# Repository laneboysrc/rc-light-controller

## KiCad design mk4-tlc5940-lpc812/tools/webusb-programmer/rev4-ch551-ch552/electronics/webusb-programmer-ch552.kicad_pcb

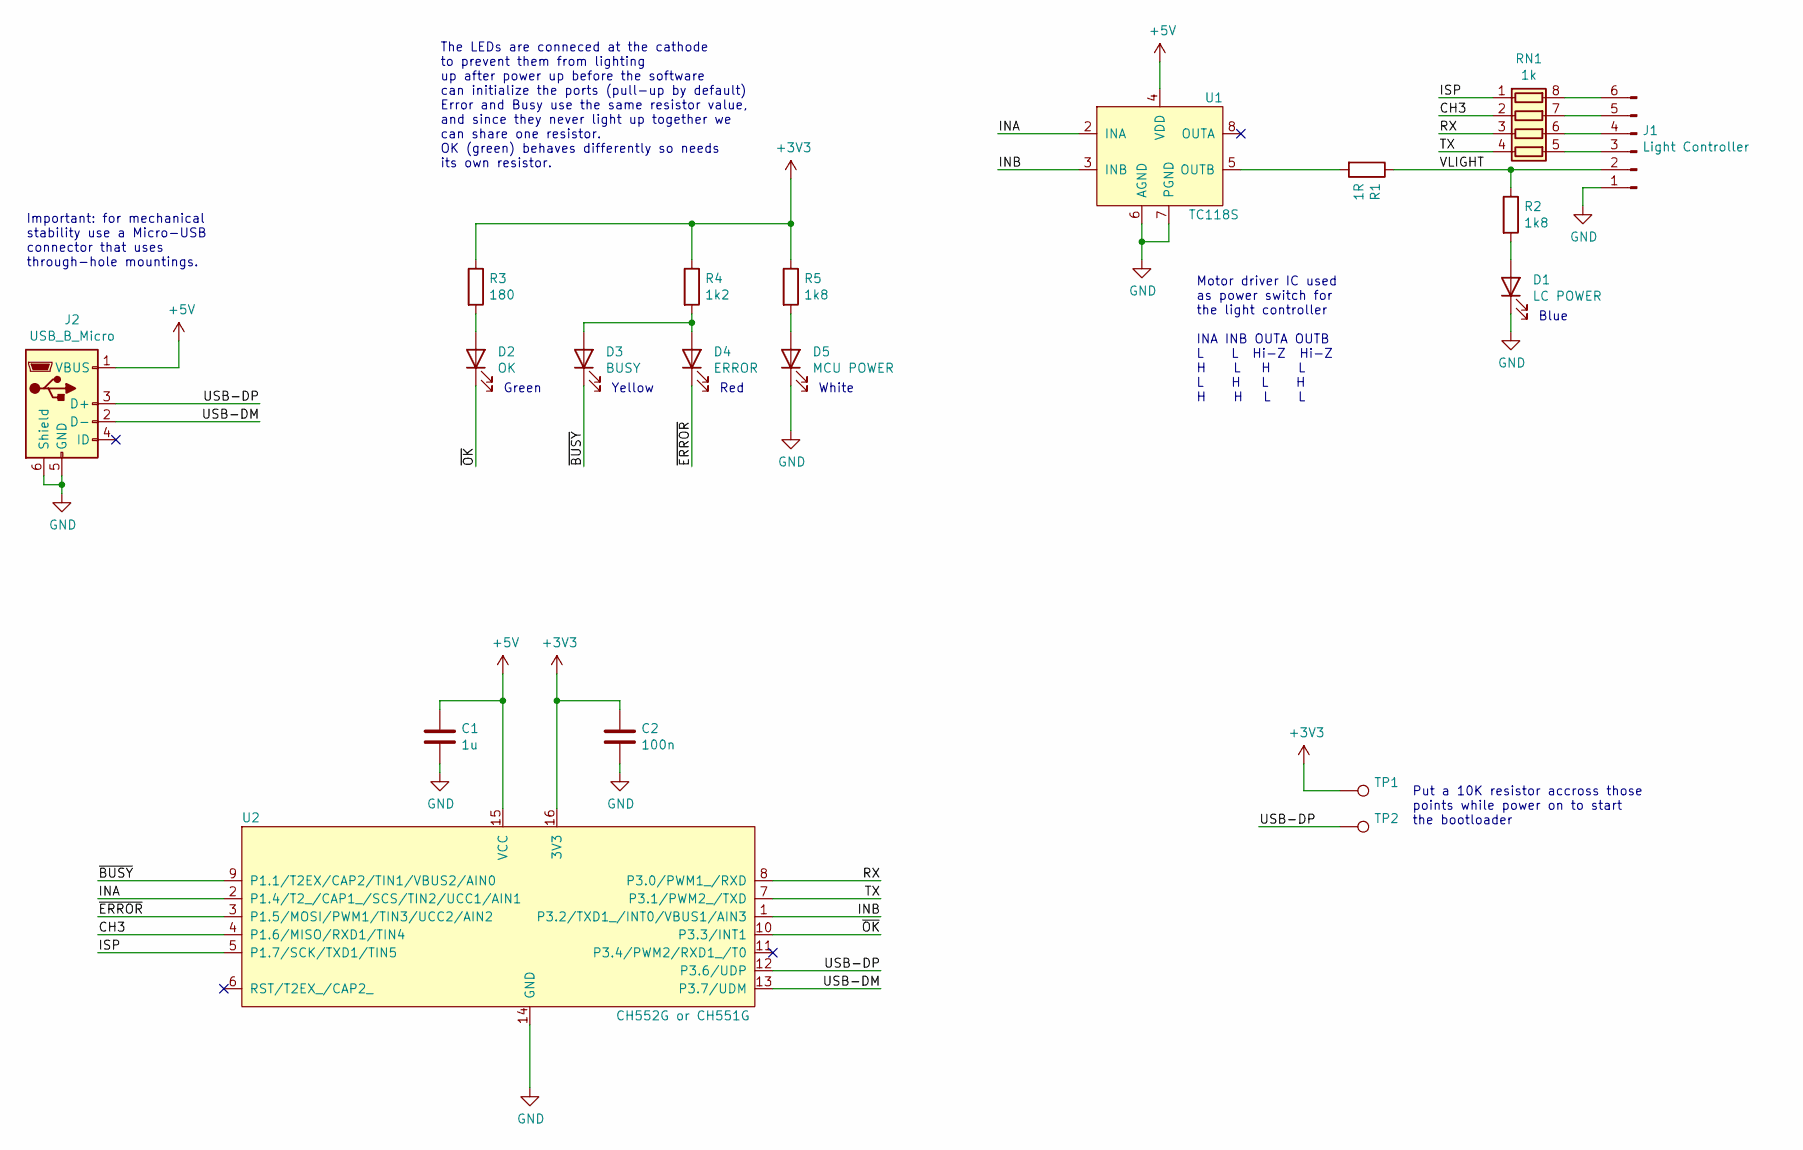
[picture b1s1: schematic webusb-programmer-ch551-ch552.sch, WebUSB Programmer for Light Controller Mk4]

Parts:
C1: 1u; C_0603_1608Metric
C2: 100n; C_0603_1608Metric
D1: LC POWER; LED_1204_side_mout; LCSC part number C779807
D2: OK; LED_1204_side_mout; LCSC part number C91608
D3: BUSY; LED_1204_side_mout; LCSC part number C779805
D4: ERROR; LED_1204_side_mout; LCSC part number C389527
D5: MCU POWER; LED_1204_side_mout; LCSC part number C779804
J1: Light Controller; PinHeader_1x06_P2.54mm_Flat
J2: USB_B_Micro; Mirco_USB_Type_B_LCSC_C40943; LCSC part number C40943
R1: 1R; R_0603_1608Metric_Pad0.98x0.95mm_HandSolder
R2, R5: 1k8; R_0603_1608Metric_Pad1.05x0.95mm_HandSolder
R3: 180; R_0603_1608Metric_Pad1.05x0.95mm_HandSolder
R4: 1k2; R_0603_1608Metric_Pad1.05x0.95mm_HandSolder
RN1: 1k; R_Array_Convex_4x0603
TP1, TP2: TestPoint_THTPad_1.0x1.0mm_Drill0.5mm_nosilk
U1: TC118S; SOP-8_3.9x4.9mm_P1.27mm
U2: CH552G or CH551G; SO-16_3.9x9.9mm_P1.27mm

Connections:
+3V3: C2.1, R3.1, R4.1, R5.1, TP1.1, U2.16 (3V3)
+5V: C1.1, J2.1 (VBUS), U1.4 (VDD), U2.15 (VCC)
/CH3: RN1.2 (R2.1), U2.4 (P1.6/MISO/RXD1/TIN4)
/INA: U1.2 (INA), U2.2 (P1.4/T2_/CAP1_/SCS/TIN2/UCC1/AIN1)
/INB: U1.3 (INB), U2.1 (P3.2/TXD1_/INT0/VBUS1/AIN3)
/ISP: RN1.1 (R1.1), U2.5 (P1.7/SCK/TXD1/TIN5)
/RX: RN1.3 (R3.1), U2.8 (P3.0/PWM1_/RXD)
/TX: RN1.4 (R4.1), U2.7 (P3.1/PWM2_/TXD)
/USB-DM: J2.2 (D-), U2.13 (P3.7/UDM)
/USB-DP: J2.3 (D+), TP2.1, U2.12 (P3.6/UDP)
/VLIGHT: J1.2, R1.1, R2.1
/~BUSY: D3.1 (K), U2.9 (P1.1/T2EX/CAP2/TIN1/VBUS2/AIN0)
/~ERROR: D4.1 (K), U2.3 (P1.5/MOSI/PWM1/TIN3/UCC2/AIN2)
/~OK: D2.1 (K), U2.10 (P3.3/INT1)
GND: C1.2, C2.2, D1.1 (K), D5.1 (K), J1.1, J2.5 (GND), J2.6 (Shield), U1.6 (AGND), U1.7 (PGND), U2.14 (GND)
unnamed: D1.2 (A), R2.2
unnamed: D2.2 (A), R3.2
unnamed: D3.2 (A), D4.2 (A), R4.2
unnamed: D5.2 (A), R5.2
unnamed: J1.3, RN1.5 (R4.2)
unnamed: J1.4, RN1.6 (R3.2)
unnamed: J1.5, RN1.7 (R2.2)
unnamed: J1.6, RN1.8 (R1.2)
unnamed: R1.2, U1.5 (OUTB)

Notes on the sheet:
Important: for mechanical stability use a Micro-USB connector that uses through-hole mountings.
White
Green
Yellow
Red
Blue
The LEDs are conneced at the cathode to prevent them from lighting up after power up before the software can initialize the ports (pull-up by default) Error and Busy use the same resistor value, and since they never light up together we can share one resistor. OK (green) behaves differently so need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
Put a 10K resistor accross those points while power on to start the bootloader
Motor driver IC used as power switch for the light controller INA INB OUTA OUTB L L Hi-Z Hi-Z H L H L L H L H H H L L

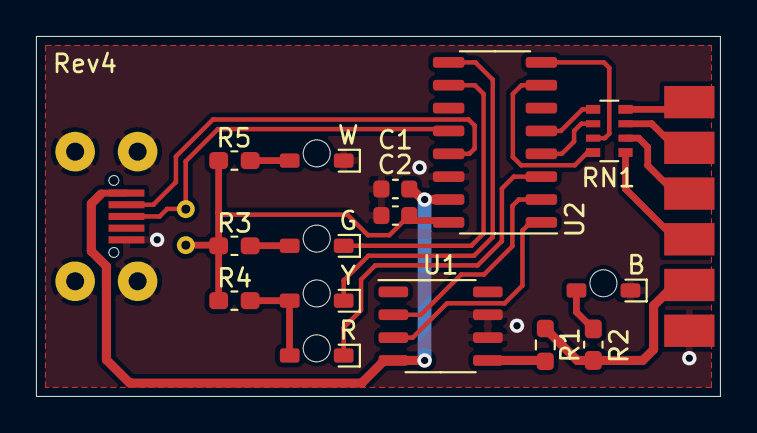
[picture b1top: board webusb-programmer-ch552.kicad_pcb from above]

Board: 2 copper layers, 38.0 x 20.0 mm, 19 parts (0 on the bottom side), 24 nets.

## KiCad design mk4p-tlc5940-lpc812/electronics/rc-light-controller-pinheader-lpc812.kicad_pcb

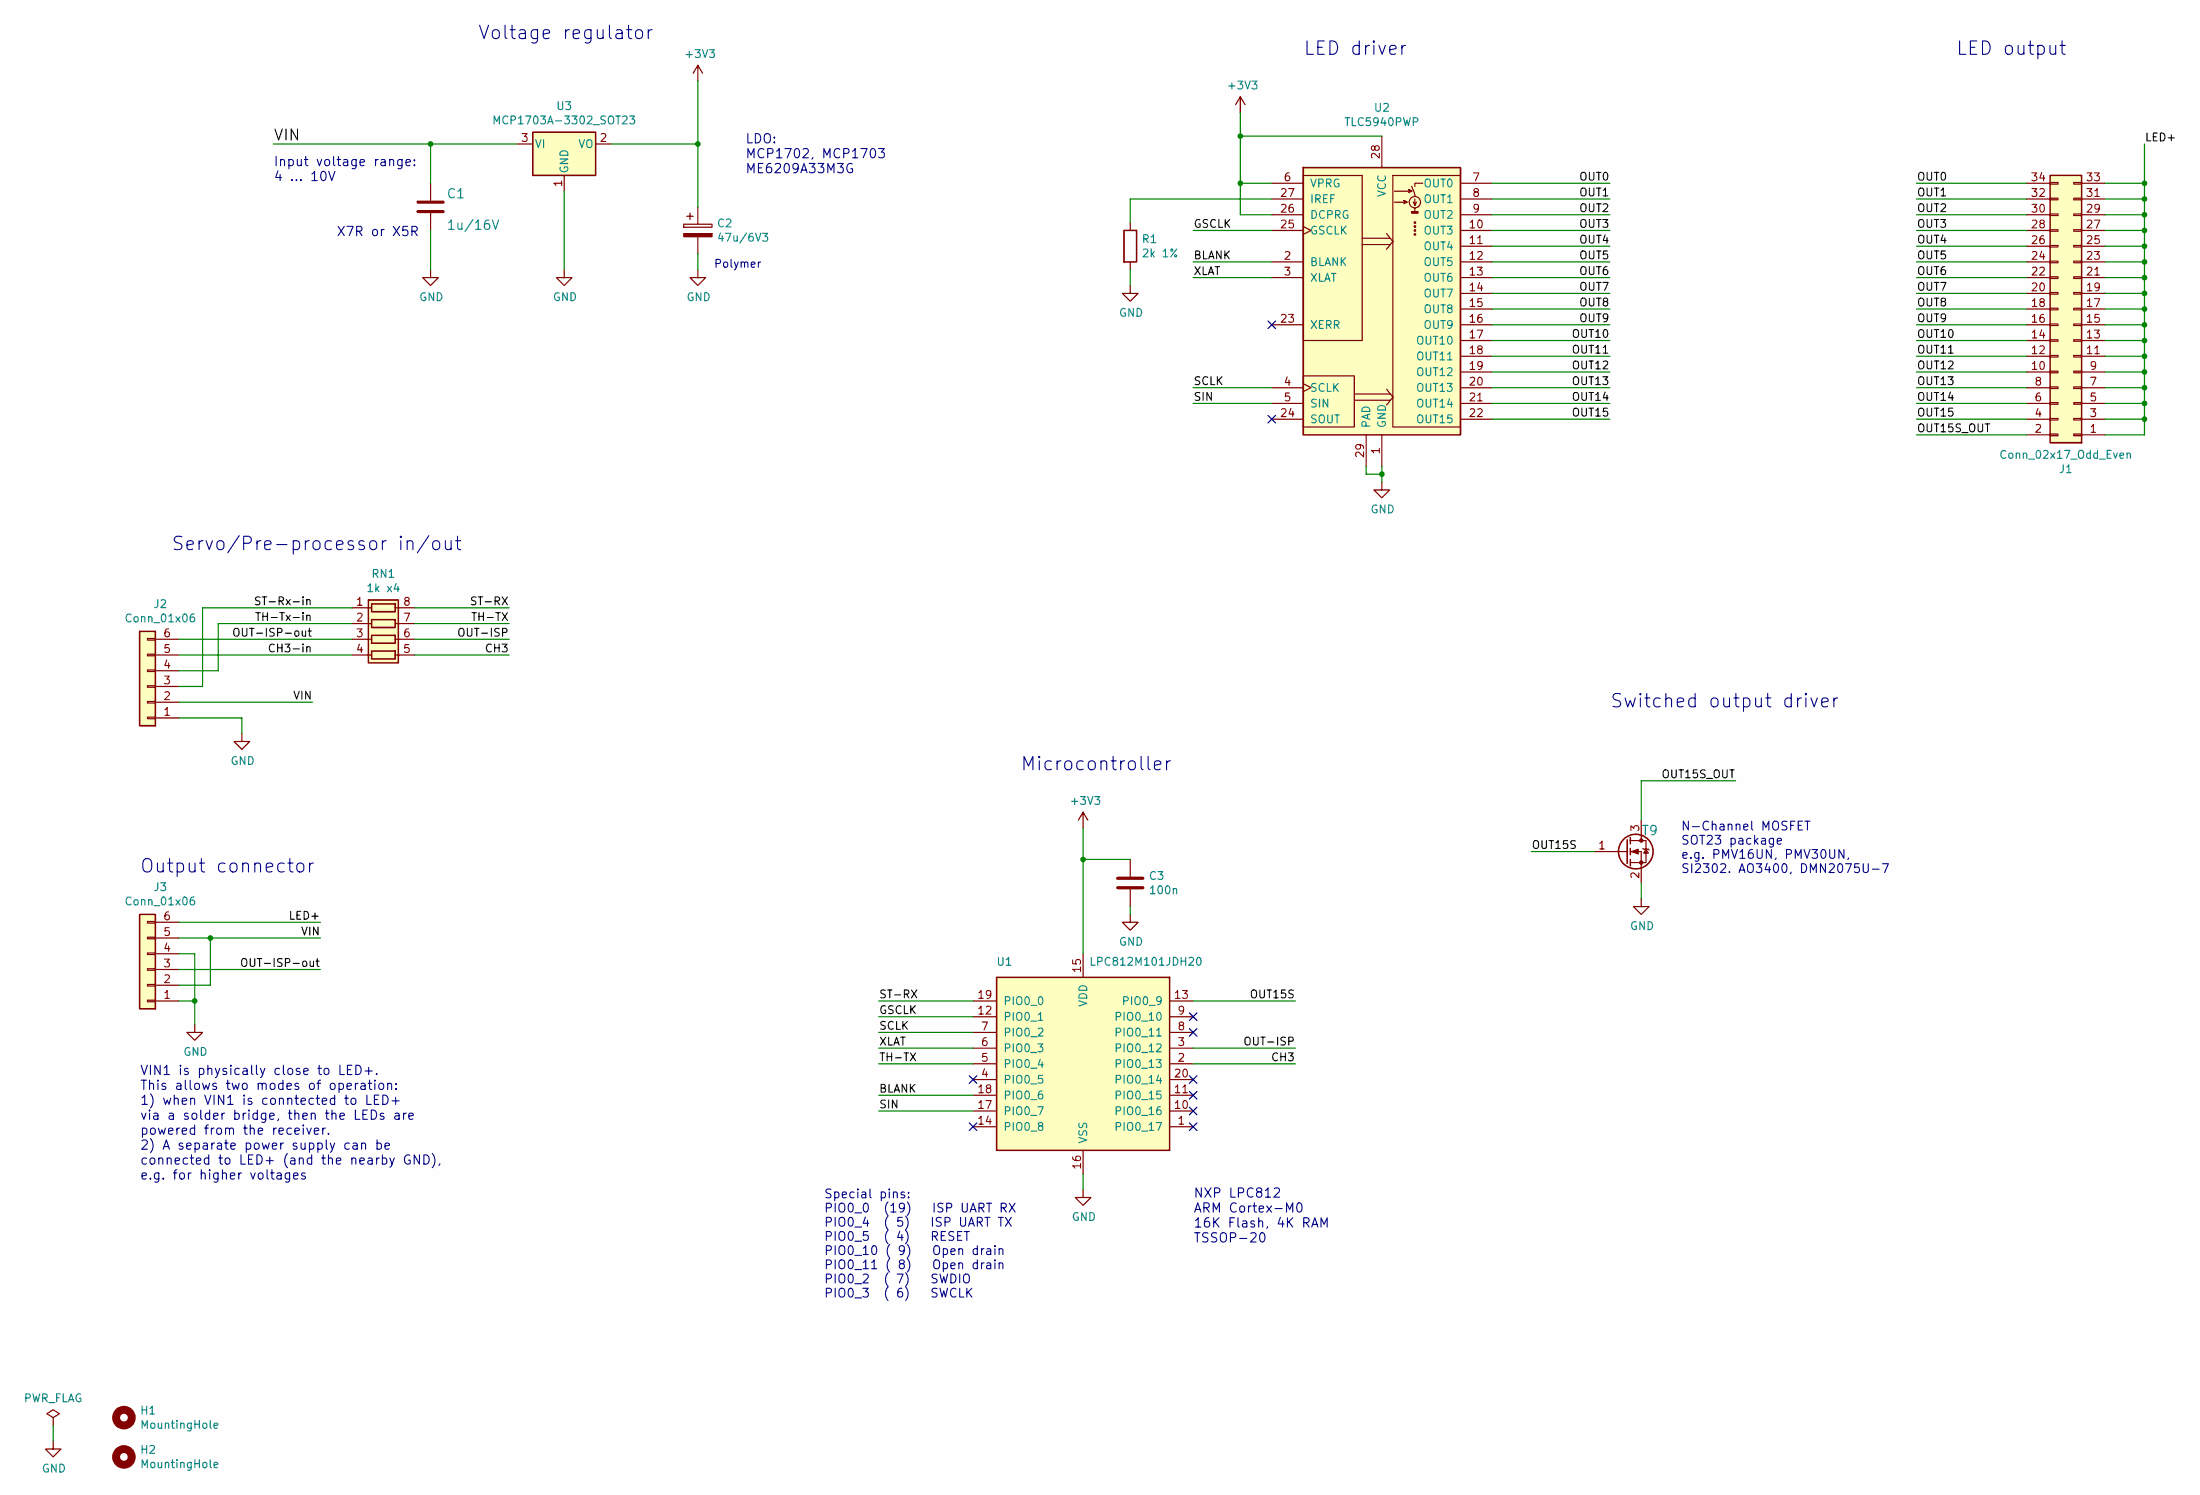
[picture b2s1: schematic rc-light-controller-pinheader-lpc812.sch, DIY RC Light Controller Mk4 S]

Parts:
C1: 1u/16V; C_0805_2012Metric
C2: 47u/6V3; C_0805_2012Metric
C3: 100n; C_0603_1608Metric
H1, H2: MountingHole; MountingHole_2.2mm_M2_ISO14580
J1: Conn_02x17_Odd_Even; PinHeader_2x17_P2.54mm_Horizontal
J2, J3: Conn_01x06; PinHeader_1x06_P2.54mm_Flat
R1: 2k 1%; R_0603_1608Metric
RN1: 1k x4; R_Array_Convex_4x0603
T9: NMOSSOT23; SOT-23
U1: LPC812M101JDH20; TSSOP-20_4.4x6.5mm_P0.65mm
U2: TLC5940PWP; SOP65P640X120-29N
U3: MCP1703A-3302_SOT23; SOT-23W

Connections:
+3V3: C2.1, C3.1, U1.15 (VDD), U2.6 (VPRG), U2.26 (DCPRG), U2.28 (VCC), U3.2 (VO)
/BLANK: U1.18 (PIO0_6), U2.2 (BLANK)
/CH3: RN1.5 (R4.2), U1.2 (PIO0_13)
/CH3-in: J2.5, RN1.4 (R4.1)
/GSCLK: U1.12 (PIO0_1), U2.25 (GSCLK)
/LED+: J1.1, J1.3, J1.5, J1.7, J1.9, J1.11, J1.13, J1.15, J1.17, J1.19, J1.21, J1.23, J1.25, J1.27, J1.29, J1.31, J1.33, J3.6
/OUT0: J1.34, U2.7 (OUT0)
/OUT1: J1.32, U2.8 (OUT1)
/OUT2: J1.30, U2.9 (OUT2)
/OUT3: J1.28, U2.10 (OUT3)
/OUT4: J1.26, U2.11 (OUT4)
/OUT5: J1.24, U2.12 (OUT5)
/OUT6: J1.22, U2.13 (OUT6)
/OUT7: J1.20, U2.14 (OUT7)
/OUT8: J1.18, U2.15 (OUT8)
/OUT9: J1.16, U2.16 (OUT9)
/OUT10: J1.14, U2.17 (OUT10)
/OUT11: J1.12, U2.18 (OUT11)
/OUT12: J1.10, U2.19 (OUT12)
/OUT13: J1.8, U2.20 (OUT13)
/OUT14: J1.6, U2.21 (OUT14)
/OUT15: J1.4, U2.22 (OUT15)
/OUT15S: T9.1 (G), U1.13 (PIO0_9)
/OUT15S_OUT: J1.2, T9.3 (D)
/OUT-ISP: RN1.6 (R3.2), U1.3 (PIO0_12)
/OUT-ISP-out: J2.6, J3.3, RN1.3 (R3.1)
/SCLK: U1.7 (PIO0_2), U2.4 (SCLK)
/SIN: U1.17 (PIO0_7), U2.5 (SIN)
/ST-RX: RN1.8 (R1.2), U1.19 (PIO0_0)
/ST-Rx-in: J2.3, RN1.1 (R1.1)
/TH-TX: RN1.7 (R2.2), U1.5 (PIO0_4)
/TH-Tx-in: J2.4, RN1.2 (R2.1)
/VIN: C1.1, J2.2, J3.2, J3.5, U3.3 (VI)
/XLAT: U1.6 (PIO0_3), U2.3 (XLAT)
GND: C1.2, C2.2, C3.2, J2.1, J3.1, J3.4, R1.2, T9.2 (S), U1.16 (VSS), U2.1 (GND), U2.29 (PAD), U3.1 (GND)
unnamed: R1.1, U2.27 (IREF)

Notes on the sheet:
Special pins: PIO0_0 (19) ISP UART RX PIO0_4 ( 5) ISP UART TX PIO0_5 ( 4) RESET PIO0_10 ( 9) Open drain PIO0_11 ( 8) Open drain PIO0_2 ( 7) SWDIO PIO0_3 ( 6) SWCLK
Servo/Pre-processor in/out
Voltage regulator
Microcontroller
X7R or X5R
Input voltage range: 4 ... 10V
LDO: MCP1702, MCP1703 ME6209A33M3G
NXP LPC812 ARM Cortex-M0 16K Flash, 4K RAM TSSOP-20
Polymer
LED output
VIN1 is physically close to LED+. This allows two modes of operation: 1) when VIN1 is conntected to LED+ via a solder bridge, then the LEDs are powered from the receiver. 2) A separate power supply can be connected to LED+ (and the nearby GND), e.g. for higher voltages
Output connector
N-Channel MOSFET SOT23 package e.g. PMV16UN, PMV30UN, SI2302. AO3400, DMN2075U-7
LED driver
Switched output driver

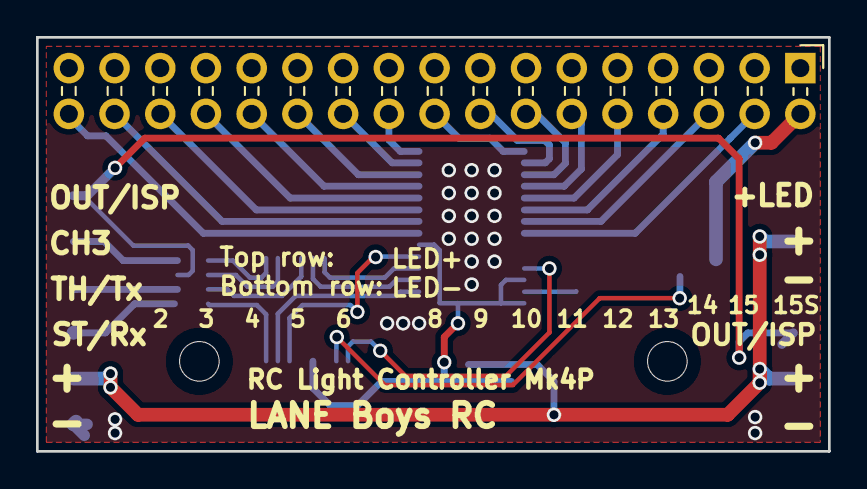
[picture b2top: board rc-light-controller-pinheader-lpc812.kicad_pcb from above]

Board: 2 copper layers, 44.0 x 23.0 mm, 14 parts (0 on the bottom side), 36 nets.

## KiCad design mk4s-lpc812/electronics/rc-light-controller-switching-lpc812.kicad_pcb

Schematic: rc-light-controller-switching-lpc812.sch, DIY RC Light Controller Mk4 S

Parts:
C1: 1u/16V; C_0805_2012Metric
C2: 47u/6V3; C_0805_2012Metric
C3: 100n; C_0603_1608Metric
H1, H2: MountingHole; MountingHole_2.2mm_M2_ISO14580
J1: Conn_02x17_Odd_Even; PinHeader_2x17_P2.54mm_Horizontal
J2, J3: Conn_01x06; PinHeader_1x06_P2.54mm_Flat
RN1: 1k x4; R_Array_Convex_4x0603
T1, T2, T3, T4, T5, T6, T7, T8, T9: NMOSSOT23; SOT-23
U1: LPC812M101JDH20; TSSOP-20_4.4x6.5mm_P0.65mm
U2: 3V3; SOT-23W

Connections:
/CH3: RN1.5 (R4.2), U1.2 (PIO0_13)
/CH3-in: J2.5, RN1.4 (R4.1)
/LED+: J1.1, J1.3, J1.5, J1.7, J1.9, J1.11, J1.13, J1.15, J1.17, J1.19, J1.21, J1.23, J1.25, J1.27, J1.29, J1.31, J1.33, J3.6
/OUT0: T1.1 (G), U1.1 (PIO0_17)
/OUT1: T2.1 (G), U1.6 (PIO0_3)
/OUT2: T3.1 (G), U1.7 (PIO0_2)
/OUT3: T4.1 (G), U1.10 (PIO0_16)
/OUT4: T5.1 (G), U1.17 (PIO0_7)
/OUT5: T6.1 (G), U1.14 (PIO0_8)
/OUT6: T7.1 (G), U1.13 (PIO0_9)
/OUT7: T8.1 (G), U1.12 (PIO0_1)
/OUT8: T9.1 (G), U1.11 (PIO0_15)
/OUT-ISP: RN1.6 (R3.2), U1.3 (PIO0_12)
/OUT-ISP-out: J2.6, J3.3, RN1.3 (R3.1)
/ST-RX: RN1.8 (R1.2), U1.19 (PIO0_0)
/ST-Rx-in: J2.3, RN1.1 (R1.1)
/TH-TX: RN1.7 (R2.2), U1.5 (PIO0_4)
/TH-Tx-in: J2.4, RN1.2 (R2.1)
/VIN: C1.1, J2.2, J3.2, J3.5, U2.3
GND: C1.2, C2.2, C3.2, J2.1, J3.1, J3.4, T1.2 (S), T2.2 (S), T3.2 (S), T4.2 (S), T5.2 (S), T6.2 (S), T7.2 (S), T8.2 (S), T9.2 (S), U1.16 (VSS), U2.1
unnamed: J1.2, T9.3 (D)
unnamed: J1.4, J1.6, T8.3 (D)
unnamed: J1.8, J1.10, T7.3 (D)
unnamed: J1.12, J1.14, T6.3 (D)
unnamed: J1.16, J1.18, T5.3 (D)
unnamed: J1.20, J1.22, T4.3 (D)
unnamed: J1.24, J1.26, T3.3 (D)
unnamed: J1.28, J1.30, T2.3 (D)
unnamed: J1.32, J1.34, T1.3 (D)

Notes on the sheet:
Special pins: PIO0_0 (19) ISP UART RX PIO0_4 ( 5) ISP UART TX PIO0_5 ( 4) RESET PIO0_10 ( 9) Open drain PIO0_11 ( 8) Open drain PIO0_2 ( 7) SWDIO PIO0_3 ( 6) SWCLK
Servo/Pre-processor in/out
Voltage regulator
Microcontroller
X7R or X5R
Input voltage range: 4 ... 10V
LDO: Microchip MCP1702 or MCP1703
NXP LPC812 ARM Cortex-M0 16K Flash, 4K RAM TSSOP-20
N-Channel MOSFET SOT23 package e.g. PMV16UN, PMV30UN, SI2302. AO3400, DMN2075U-7
Polymer
LED driver and outputs
VIN1 is physically close to LED+. This allows two modes of operation: 1) when VIN1 is conntected to LED+ via a solder bridge, then the LEDs are powered from the receiver. 2) A separate power supply can be connected to LED+ (and the nearby GND), e.g. for higher voltages
Output connector

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
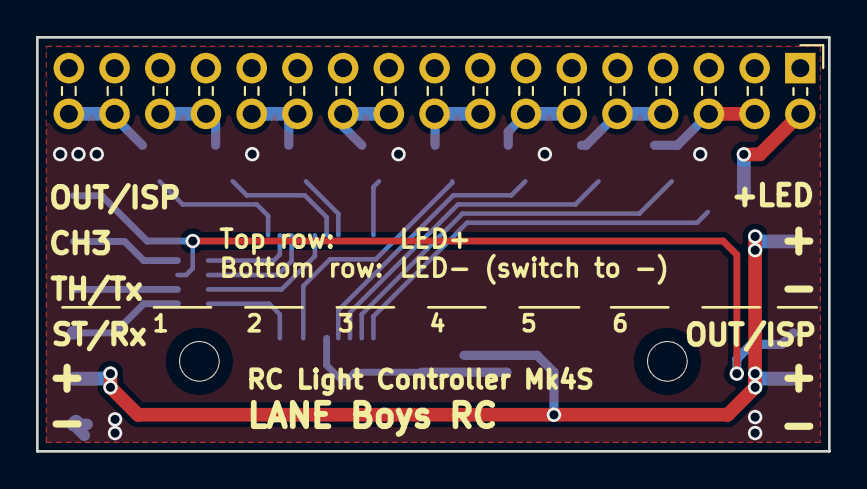
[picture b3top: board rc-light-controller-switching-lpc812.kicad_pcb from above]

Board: 2 copper layers, 44.0 x 23.0 mm, 20 parts (0 on the bottom side), 30 nets.

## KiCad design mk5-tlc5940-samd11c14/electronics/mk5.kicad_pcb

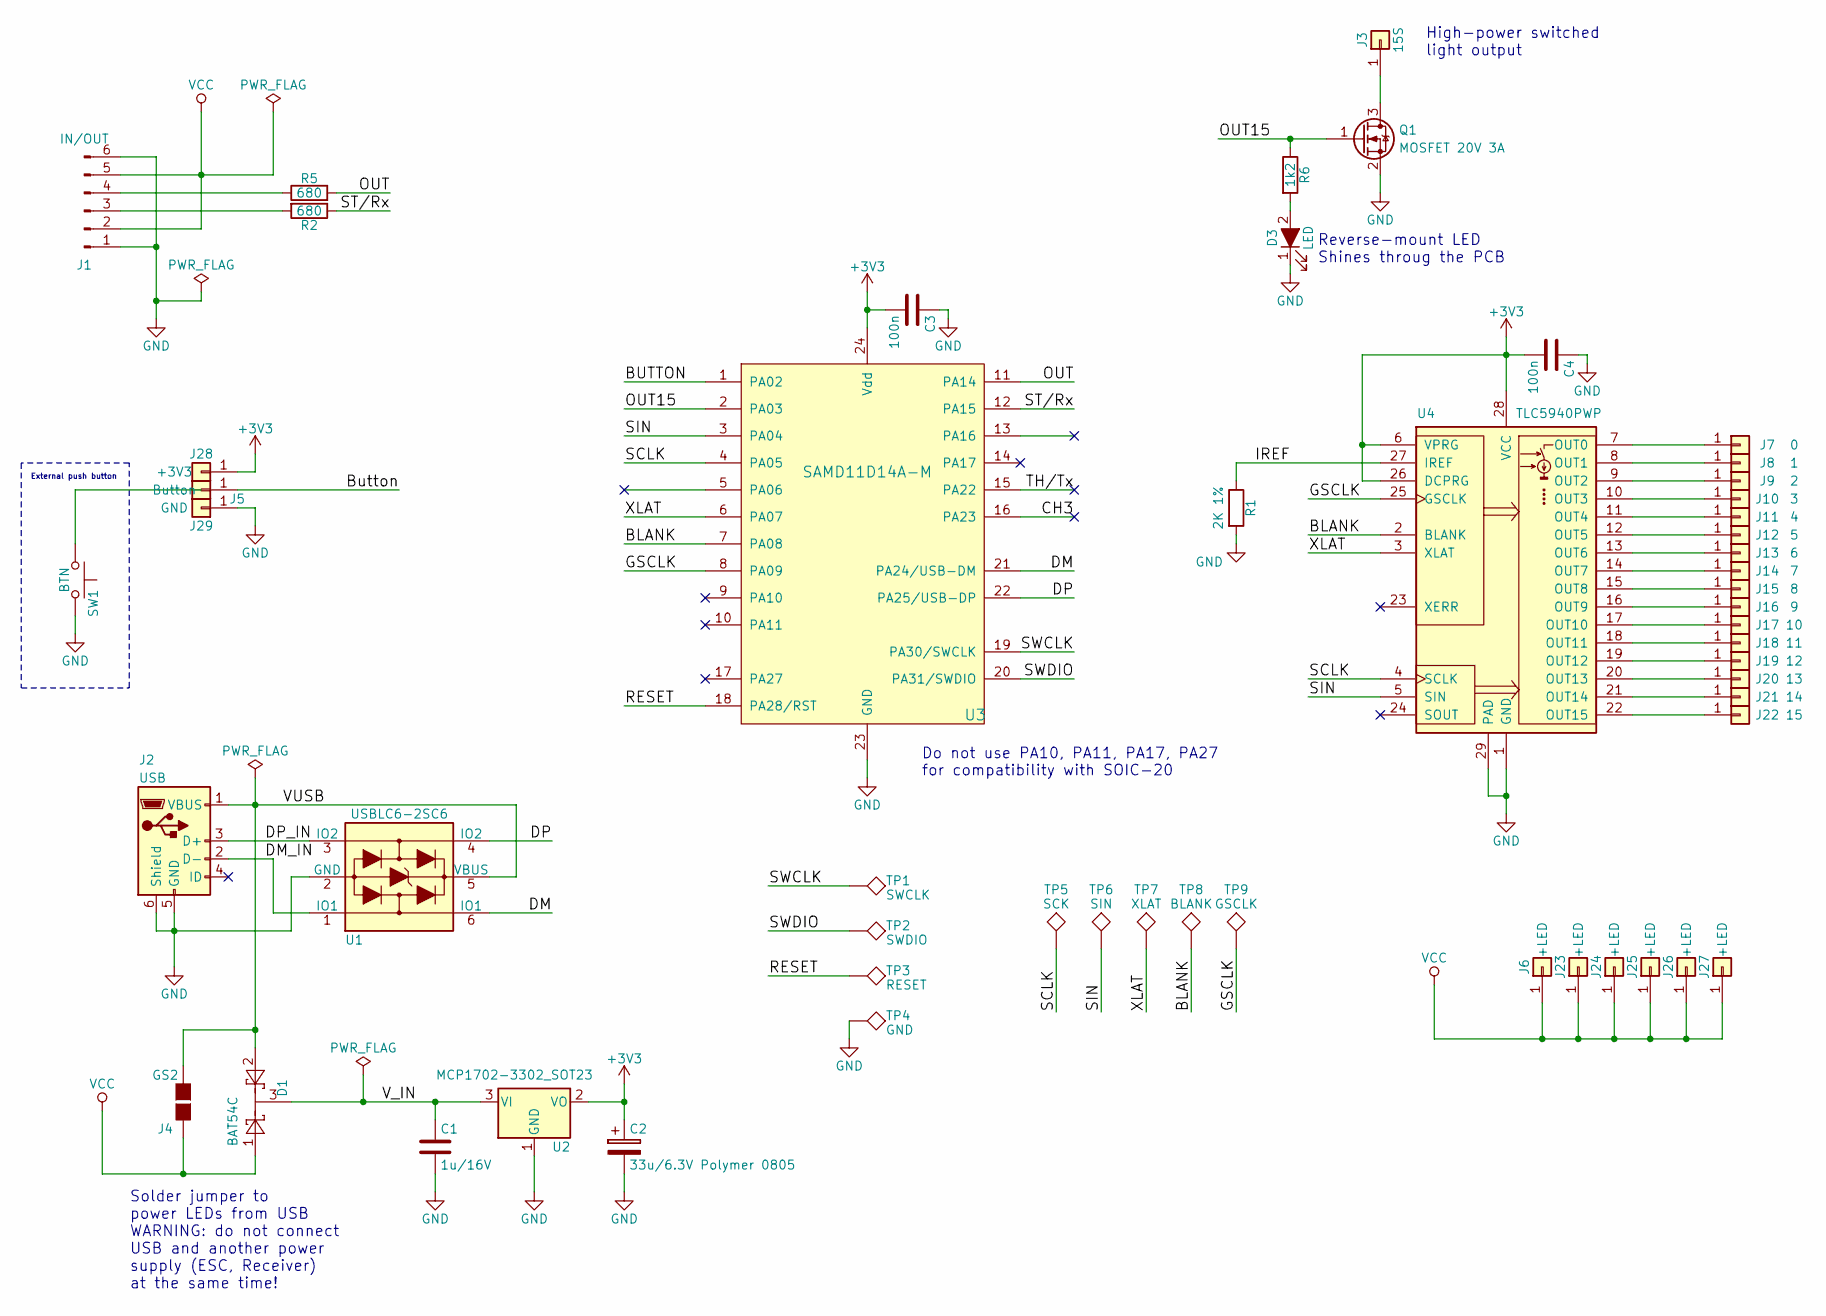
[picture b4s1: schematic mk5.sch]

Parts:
C1: 1u/16V; C_0805
C2: 33u/6.3V Polymer 0805; C_0805
C3, C4: 100n; C_0603
D1: BAT54C; SOT-23
D3: LED; REVERSE_MOUNT_ROHM_SLM-81
J1: IN/OUT; CONN_6_SMD_FLAT
J2: USB; Mirco_USB_Type_B_eBay_AliExpress
J3: 15S; SMD50x100
J4: GS2; SMD_solder_jumper_2pin
J5: +3V3; Measurement_Point_Round-SMD-Pad_Small
J6, J23, J24, J25, J26, J27: +LED; SMD50x100
J7: 0; SMD50x100
J8: 1; SMD50x100
J9: 2; SMD50x100
J10: 3; SMD50x100
J11: 4; SMD50x100
J12: 5; SMD50x100
J13: 6; SMD50x100
J14: 7; SMD50x100
J15: 8; SMD50x100
J16: 9; SMD50x100
J17: 10; SMD50x100
J18: 11; SMD50x100
J19: 12; SMD50x100
J20: 13; SMD50x100
J21: 14; SMD50x100
J22: 15; SMD50x100
J28: Button; Measurement_Point_Round-SMD-Pad_Small
J29: GND; Measurement_Point_Round-SMD-Pad_Small
Q1: MOSFET 20V 3A; SOT-23
R1: 2K 1%; R_0805_HandSoldering
R2, R5: 680; R_0603
R6: 1k2; R_0603
SW1: BTN; SW_SPST_SKQG
TP1: SWCLK; Measurement_Point_Round-SMD-Pad_Small
TP2: SWDIO; Measurement_Point_Round-SMD-Pad_Small
TP3: RESET; Measurement_Point_Round-SMD-Pad_Small
TP4: GND; Measurement_Point_Round-SMD-Pad_Small
TP5: SCK; Measurement_Point_Round-SMD-Pad_0_6mm
TP6: SIN; Measurement_Point_Round-SMD-Pad_0_6mm
TP7: XLAT; Measurement_Point_Round-SMD-Pad_0_6mm
TP8: BLANK; Measurement_Point_Round-SMD-Pad_0_6mm
TP9: GSCLK; Measurement_Point_Round-SMD-Pad_0_6mm
U1: USBLC6-2SC6; SOT-23-6
U2: MCP1702-3302_SOT23; SOT-23
U3: SAMD11D14A-M; QFN-24_4x4mm_Pitch0.5mm
U4: TLC5940PWP; HTSSOP-28_4.4x9.7mm_Pitch0.65mm_ThermalPad_paste

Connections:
+3V3: C2.1, C3.2, C4.2, J5.1, U2.2 (VO), U3.24 (Vdd), U4.6 (VPRG), U4.26 (DCPRG), U4.28 (VCC)
/BLANK: TP8.1, U3.7 (PA08), U4.2 (BLANK)
/BUTTON: J28.1, U3.1 (PA02)
/CH3: U3.16 (PA23)
/DM: U1.6 (IO1), U3.21 (PA24/USB-DM)
/DM_IN: J2.2 (D-), U1.1 (IO1)
/DP: U1.4 (IO2), U3.22 (PA25/USB-DP)
/DP_IN: J2.3 (D+), U1.3 (IO2)
/GSCLK: TP9.1, U3.8 (PA09), U4.25 (GSCLK)
/IREF: R1.1, U4.27 (IREF)
/OUT: R5.2, U3.11 (PA14)
/OUT15: Q1.1 (G), R6.1, U3.2 (PA03)
/RESET: TP3.1, U3.18 (PA28/RST)
/SCLK: TP5.1, U3.4 (PA05), U4.4 (SCLK)
/SIN: TP6.1, U3.3 (PA04), U4.5 (SIN)
/ST/Rx: R2.1, U3.12 (PA15)
/SWCLK: TP1.1, U3.19 (PA30/SWCLK)
/SWDIO: TP2.1, U3.20 (PA31/SWDIO)
/TH/Tx: U3.15 (PA22)
/VUSB: D1.2, J2.1 (VBUS), J4.2 (G2), U1.5 (VBUS)
/V_IN: C1.1, D1.3, U2.3 (VI)
/XLAT: TP7.1, U3.6 (PA07), U4.3 (XLAT)
GND: C1.2, C2.2, C3.1, C4.1, D3.1 (K), J1.1, J1.6, J2.5 (GND), J2.6 (Shield), J29.1, Q1.2 (S), R1.2, SW1.2, TP4.1, U1.2 (GND), U2.1 (GND), U3.23 (GND), U4.1 (GND), U4.29 (PAD)
unnamed: D3.2 (A), R6.2
unnamed: J1.3, R2.2
unnamed: J1.4, R5.1
unnamed: J3.1, Q1.3 (D)
unnamed: J7.1, U4.7 (OUT0)
unnamed: J8.1, U4.8 (OUT1)
unnamed: J9.1, U4.9 (OUT2)
unnamed: J10.1, U4.10 (OUT3)
unnamed: J11.1, U4.11 (OUT4)
unnamed: J12.1, U4.12 (OUT5)
unnamed: J13.1, U4.13 (OUT6)
unnamed: J14.1, U4.14 (OUT7)
unnamed: J15.1, U4.15 (OUT8)
unnamed: J16.1, U4.16 (OUT9)
unnamed: J17.1, U4.17 (OUT10)
unnamed: J18.1, U4.18 (OUT11)
unnamed: J19.1, U4.19 (OUT12)
unnamed: J20.1, U4.20 (OUT13)
unnamed: J21.1, U4.21 (OUT14)
unnamed: J22.1, U4.22 (OUT15)
VCC: D1.1, J1.2, J1.5, J4.1 (G1), J6.1, J23.1, J24.1, J25.1, J26.1, J27.1

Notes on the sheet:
Do not use PA10, PA11, PA17, PA27 for compatibility with SOIC-20
External push button
Reverse-mount LED Shines throug the PCB
High-power switched light output
Solder jumper to power LEDs from USB WARNING: do not connect USB and another power supply (ESC, Receiver) at the same time!

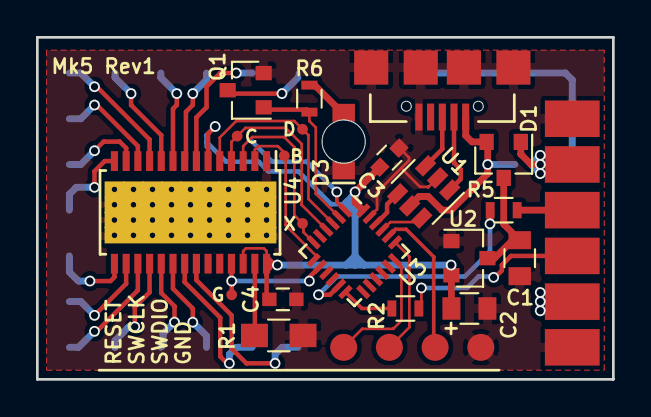
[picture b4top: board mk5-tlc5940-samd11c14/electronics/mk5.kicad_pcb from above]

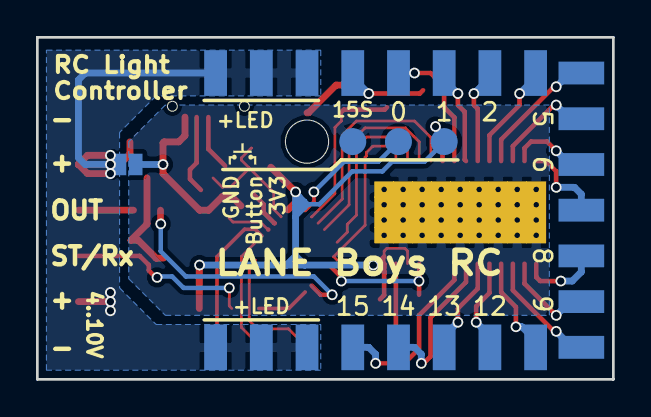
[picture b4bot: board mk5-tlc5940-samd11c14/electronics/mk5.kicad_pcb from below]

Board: 2 copper layers, 32.0 x 19.0 mm, 53 parts (27 on the bottom side), 42 nets.

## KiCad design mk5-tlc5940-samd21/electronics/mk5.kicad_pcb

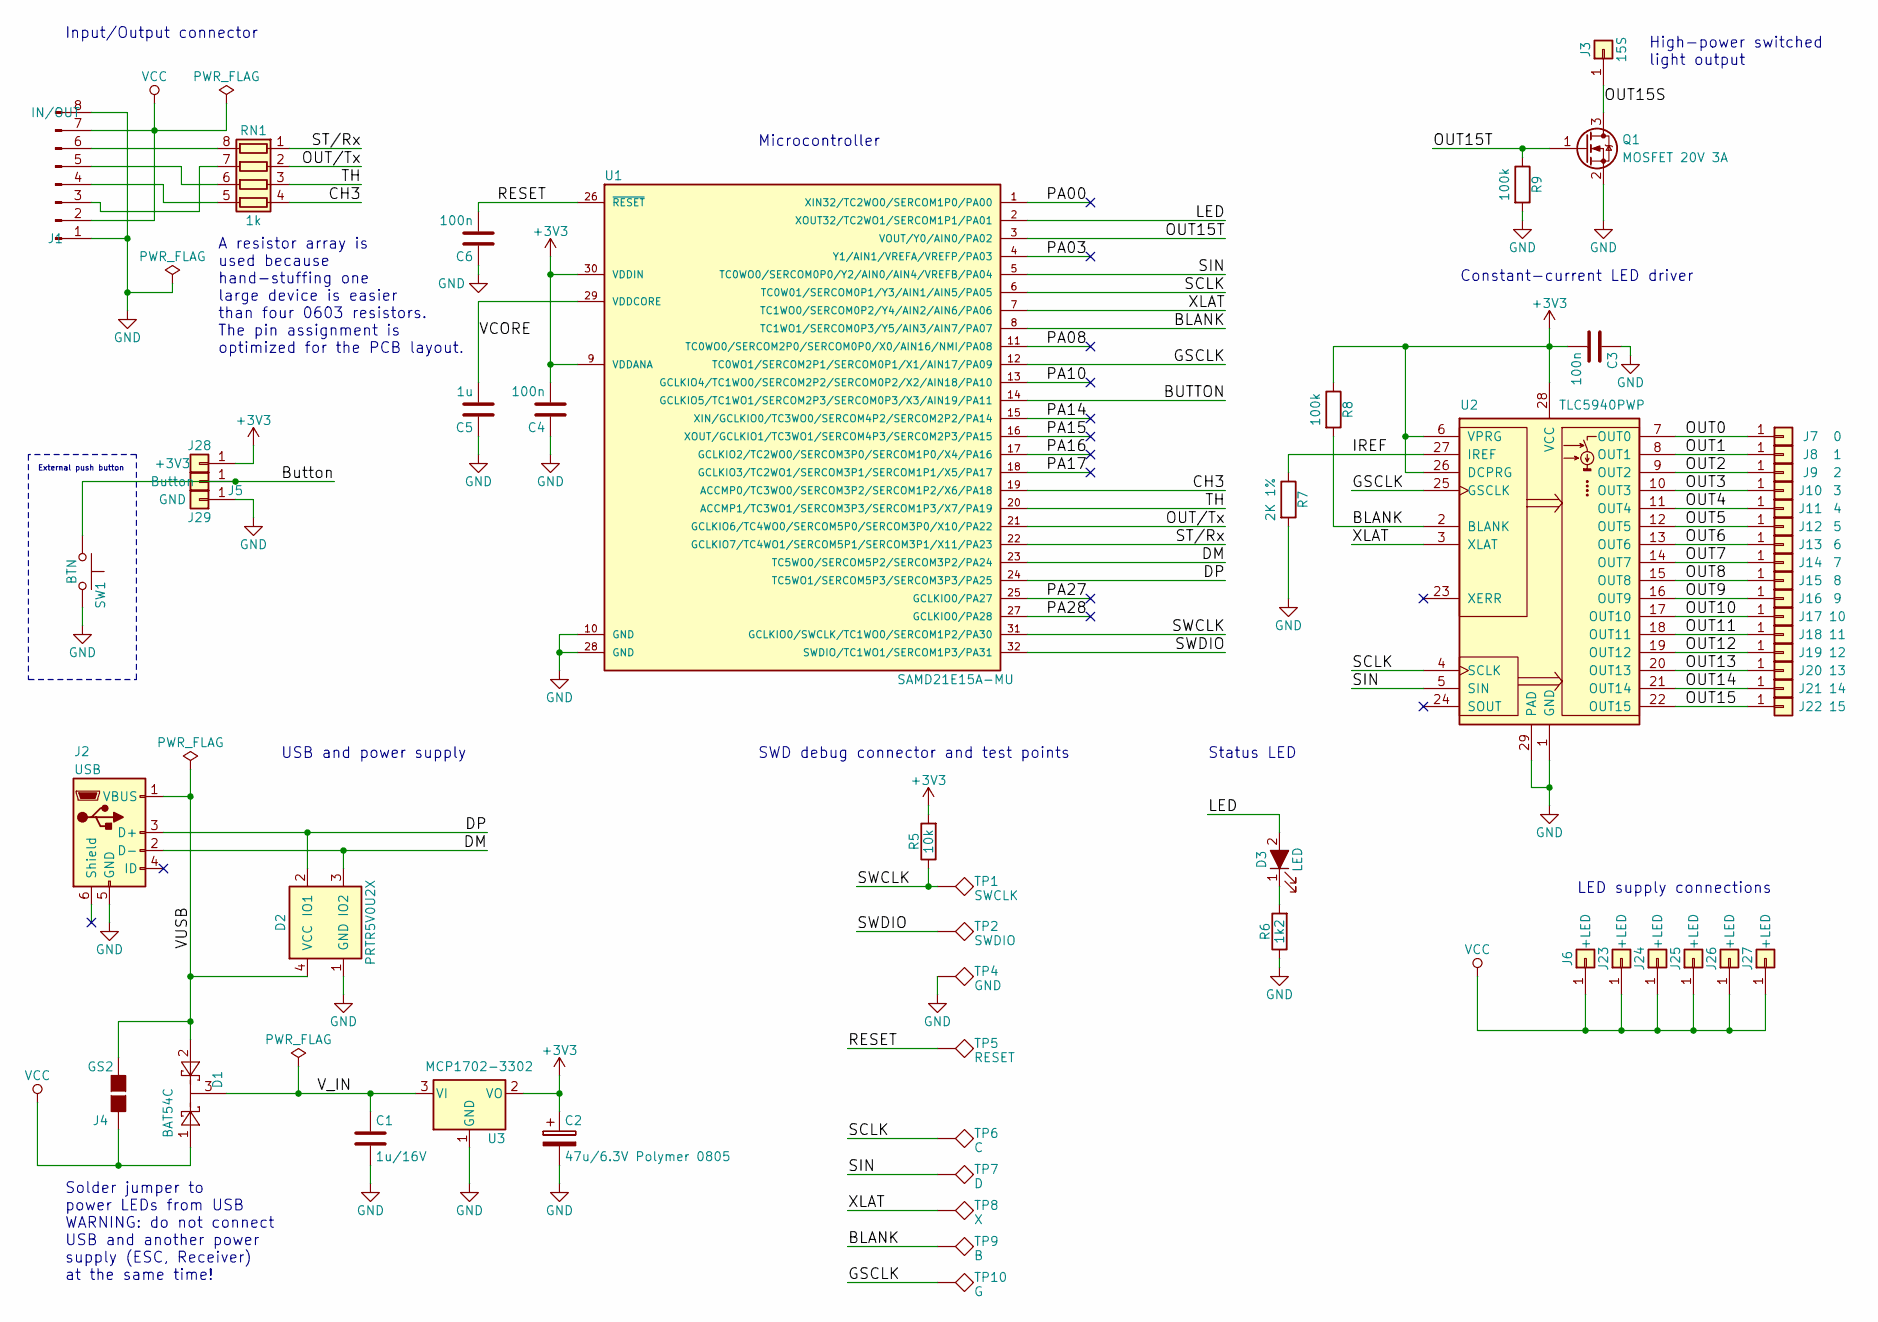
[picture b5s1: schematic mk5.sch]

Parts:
C1: 1u/16V; C_0805
C2: 47u/6.3V Polymer 0805; C_0805
C3, C4, C6: 100n; C_0603
C5: 1u; C_0603
D1: BAT54C; SOT-23
D2: PRTR5V0U2X; SOT143B
D3: LED; LED_0603
J1: IN/OUT; CONN_8_SMD_FLAT
J2: USB; Mirco_USB_Type_B_eBay_AliExpress
J3: 15S; SMD50x100
J4: GS2; SMD_solder_jumper_2pin
J5: +3V3; Measurement_Point_Round-SMD-Pad_Small
J6, J23, J24, J25, J26, J27: +LED; SMD50x100
J7: 0; SMD50x100
J8: 1; SMD50x100
J9: 2; SMD50x100
J10: 3; SMD50x100
J11: 4; SMD50x100
J12: 5; SMD50x100
J13: 6; SMD50x100
J14: 7; SMD50x100
J15: 8; SMD50x100
J16: 9; SMD50x100
J17: 10; SMD50x100
J18: 11; SMD50x100
J19: 12; SMD50x100
J20: 13; SMD50x100
J21: 14; SMD50x100
J22: 15; SMD50x100
J28: Button; Measurement_Point_Round-SMD-Pad_Small
J29: GND; Measurement_Point_Round-SMD-Pad_Small
Q1: MOSFET 20V 3A; SOT-23
R5: 10k; R_0603
R6: 1k2; R_0603
R7: 2K 1%; R_0603
R8, R9: 100k; R_0603
RN1: 1k; R_Array_Convex_4x0603
SW1: BTN
TP1: SWCLK; Pin_Header_Straight_1x01_Pitch2.54mm_no_3D_model
TP2: SWDIO; Pin_Header_Straight_1x01_Pitch2.54mm_no_3D_model
TP4: GND; Pin_Header_Straight_1x01_Pitch2.54mm_no_3D_model
TP5: RESET; Measurement_Point_Round-SMD-Pad_1mm
TP6: C; Measurement_Point_Round-SMD-Pad_1mm
TP7: D; Measurement_Point_Round-SMD-Pad_1mm
TP8: X; Measurement_Point_Round-SMD-Pad_1mm
TP9: B; Measurement_Point_Round-SMD-Pad_1mm
TP10: G; Measurement_Point_Round-SMD-Pad_1mm
U1: SAMD21E15A-MU; QFN-32-1EP_5x5mm_Pitch0.5mm
U2: TLC5940PWP; HTSSOP-28_4.4x9.7mm_Pitch0.65mm_ThermalPad_paste
U3: MCP1702-3302; SOT-23

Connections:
+3V3: C2.1, C3.2, C4.2, J5.1, R5.2, R8.1, U1.9 (VDDANA), U1.30 (VDDIN), U2.6 (VPRG), U2.26 (DCPRG), U2.28 (VCC), U3.2 (VO)
/BLANK: R8.2, TP9.1, U1.8 (TC1WO1/SERCOM0P3/Y5/AIN3/AIN7/PA07), U2.2 (BLANK)
/BUTTON: J28.1, SW1.1, U1.14 (GCLKIO5/TC1WO1/SERCOM2P3/SERCOM0P3/X3/A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)
/CH3: RN1.4 (R4.1), U1.19 (ACCMP0/TC3WO0/SERCOM3P2/SERCOM1P2/X6/PA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)
/DM: D2.3 (IO2), J2.2 (D-), U1.23 (TC5WO0/SERCOM5P2/SERCOM3P2/PA24)
/DP: D2.2 (IO1), J2.3 (D+), U1.24 (TC5WO1/SERCOM5P3/SERCOM3P3/PA25)
/GSCLK: TP10.1, U1.12 (TC0WO1/SERCOM2P1/SERCOM0P1/X1/AIN17/PA09), U2.25 (GSCLK)
/IREF: R7.1, U2.27 (IREF)
/LED: D3.2 (A), U1.2 (XOUT32/TC2WO1/SERCOM1P1/PA01)
/OUT0: J7.1, U2.7 (OUT0)
/OUT1: J8.1, U2.8 (OUT1)
/OUT2: J9.1, U2.9 (OUT2)
/OUT3: J10.1, U2.10 (OUT3)
/OUT4: J11.1, U2.11 (OUT4)
/OUT5: J12.1, U2.12 (OUT5)
/OUT6: J13.1, U2.13 (OUT6)
/OUT7: J14.1, U2.14 (OUT7)
/OUT8: J15.1, U2.15 (OUT8)
/OUT9: J16.1, U2.16 (OUT9)
/OUT10: J17.1, U2.17 (OUT10)
/OUT11: J18.1, U2.18 (OUT11)
/OUT12: J19.1, U2.19 (OUT12)
/OUT13: J20.1, U2.20 (OUT13)
/OUT14: J21.1, U2.21 (OUT14)
/OUT15: J22.1, U2.22 (OUT15)
/OUT15S: J3.1, Q1.3 (D)
/OUT15T: Q1.1 (G), R9.1, U1.3 (VOUT/Y0/AIN0/PA02)
/OUT/Tx: RN1.2 (R2.1), U1.21 (GCLKIO6/TC4WO0/SERCOM5P0/SERCOM3P0/X10/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)
/PA00: U1.1 (XIN32/TC2WO0/SERCOM1P0/PA00)
/PA03: U1.4 (Y1/AIN1/VREFA/VREFP/PA03)
/PA08: U1.11 (TC0WO0/SERCOM2P0/SERCOM0P0/X0/AIN16/NMI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)
/PA10: U1.13 (GCLKIO4/TC1WO0/SERCOM2P2/SERCOM0P2/X2/A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)
/PA14: U1.15 (XIN/GCLKIO0/TC3WO0/SERCOM4P2/SERCOM2P2/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)
/PA15: U1.16 (XOUT/GCLKIO1/TC3WO1/SERCOM4P3/SERCOM2P3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)
/PA16: U1.17 (GCLKIO2/TC2WO0/SERCOM3P0/SERCOM1P0/X4/P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)
/PA17: U1.18 (GCLKIO3/TC2WO1/SERCOM3P1/SERCOM1P1/X5/P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)
/PA27: U1.25 (GCLKIO0/PA27)
/PA28: U1.27 (GCLKIO0/PA28)
/RESET: C6.2, TP5.1, U1.26 (~RESET~)
/SCLK: TP6.1, U1.6 (TC0W01/SERCOM0P1/Y3/AIN1/AIN5/PA05), U2.4 (SCLK)
/SIN: TP7.1, U1.5 (TC0WO0/SERCOM0P0/Y2/AIN0/AIN4/VREFB/PA04), U2.5 (SIN)
/ST/Rx: RN1.1 (R1.1), U1.22 (GCLKIO7/TC4WO1/SERCOM5P1/SERCOM3P1/X11/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)
/SWCLK: R5.1, TP1.1, U1.31 (GCLKIO0/SWCLK/TC1WO0/SERCOM1P2/PA30)
/SWDIO: TP2.1, U1.32 (SWDIO/TC1WO1/SERCOM1P3/PA31)
/TH: RN1.3 (R3.1), U1.20 (ACCMP1/TC3WO1/SERCOM3P3/SERCOM1P3/X7/PA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)
/VCORE: C5.2, U1.29 (VDDCORE)
/VUSB: D1.2, D2.4 (VCC), J2.1 (VBUS), J4.2 (G2)
/V_IN: C1.1, D1.3, U3.3 (VI)
/XLAT: TP8.1, U1.7 (TC1WO0/SERCOM0P2/Y4/AIN2/AIN6/PA06), U2.3 (XLAT)
GND: C1.2, C2.2, C3.1, C4.1, C5.1, C6.1, D2.1 (GND), J1.1, J1.8, J2.5 (GND), J29.1, Q1.2 (S), R6.1, R7.2, R9.2, SW1.2, TP4.1, U1.10 (GND), U1.28 (GND), U2.1 (GND), U2.29 (PAD), U3.1 (GND)
unnamed: D3.1 (K), R6.2
unnamed: J1.3, RN1.7 (R2.2)
unnamed: J1.4, RN1.5 (R4.2)
unnamed: J1.5, RN1.6 (R3.2)
unnamed: J1.6, RN1.8 (R1.2)
VCC: D1.1, J1.2, J1.7, J4.1 (G1), J6.1, J23.1, J24.1, J25.1, J26.1, J27.1

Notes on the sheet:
External push button
High-power switched light output
Solder jumper to power LEDs from USB WARNING: do not connect USB and another power supply (ESC, Receiver) at the same time!
USB and power supply
Microcontroller
Input/Output connector
SWD debug connector and test points
Status LED
Constant-current LED driver
LED supply connections
A resistor array is used because hand-stuffing one large device is easier than four 0603 resistors. The pin assignment is optimized for the PCB layout.

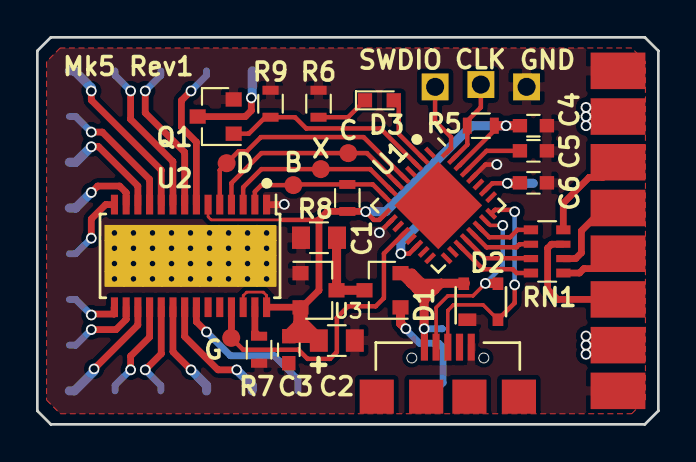
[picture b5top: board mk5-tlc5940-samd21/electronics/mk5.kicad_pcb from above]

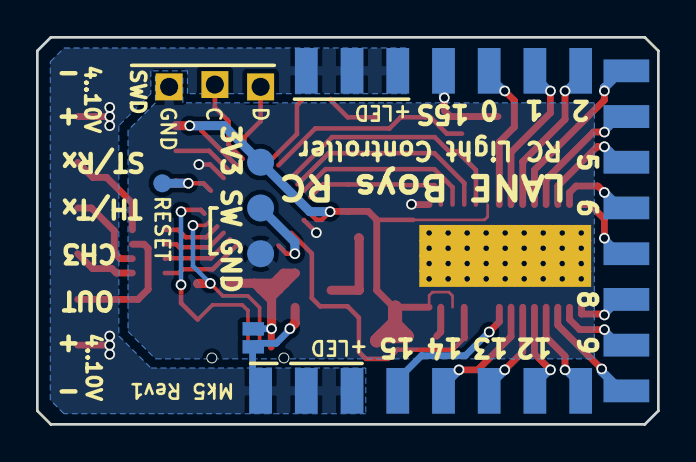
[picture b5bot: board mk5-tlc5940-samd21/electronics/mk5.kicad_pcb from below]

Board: 2 copper layers, 34.5 x 21.5 mm, 57 parts (28 on the bottom side), 46 nets.
